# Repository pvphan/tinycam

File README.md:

tinycam
---

This is a simple point-and-shoot camera, mostly an excuse to play with the new [Raspberry Pi High Quality camera](https://www.raspberrypi.org/products/raspberry-pi-high-quality-camera/) and ~~maybe~~ **also** a simple PCB for battery management.
The code is a very simple python script wrapping `raspistill`.
CAD is in [FreeCAD](https://www.freecadweb.org/), and any PCBs designed will be [KiCAD](https://kicad-pcb.org/).

Hardware requirements:

- [Raspberry Pi Zero W ($25)](https://www.amazon.com/CanaKit-Raspberry-Wireless-Official-Supply/dp/B071L2ZQZX/)
- [Samsung Evo+ 32 GB microSD card ($9)](https://www.amazon.com/gp/product/B00WR4IJBE)
- [iUniker 2.8" display ($23)](https://www.amazon.com/gp/product/B07H8ZY89H/)
- [Raspberry Pi High Quality camera ($50)](https://www.pishop.us/product/raspberry-pi-hq-camera/?src=raspberrypi)
- [Telephoto lens for HQ camera ($63)](https://www.pishop.us/product/16mm-telephoto-lens-for-raspberry-pi-hq-camera/)
- [Adafruit PowerBoost 1000 Charger ($20)](https://www.adafruit.com/product/2465)
- [tinycam PCB (~$35 to build)](pcb/)

#### next TODO:

- v2 of chassis to support button trigger and battery management
- auto upload to gphotos a la [eshmu/gphotos-upload](https://github.com/eshmu/gphotos-upload)
- support sleep / wake mode
- gallery mode (for local delete)

#### maybe later TODO:

- support video capture mode
- Qt overlay on top of preview for mode switching or adjusting 'manual' controls

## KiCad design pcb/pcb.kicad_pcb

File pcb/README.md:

PCB
---

**WARNING: as of 2020-10-04, this design does not yet work! There is at least one significant deficiency in the PCB layout around the boost converter (TPS61090). I'm still working through the issues, but here are some links to seemingly related problems:**

- [Adafruit board with similar symptoms](https://forums.adafruit.com/viewtopic.php?f=19&t=110556&start=15)
- [TI forum - TPS61090: short circuits at SW pin 3,4 after working for some time](https://e2e.ti.com/support/power-management/f/196/t/642142?TPS61090-short-circuits-at-SW-pin-3-4-after-working-for-some-time)

PCB designed in KiCAD, BOM in DigiKey importable format ([pcb.csv](pcb.csv)).
The PCB is [shared on OSHPark](https://oshpark.com/shared_projects/fBtFeIY9), cost is $11.90 for 3x board with normal prototyping service.

### 3D Model:

### Schematic:

### PCB Front:

### PCB Back:

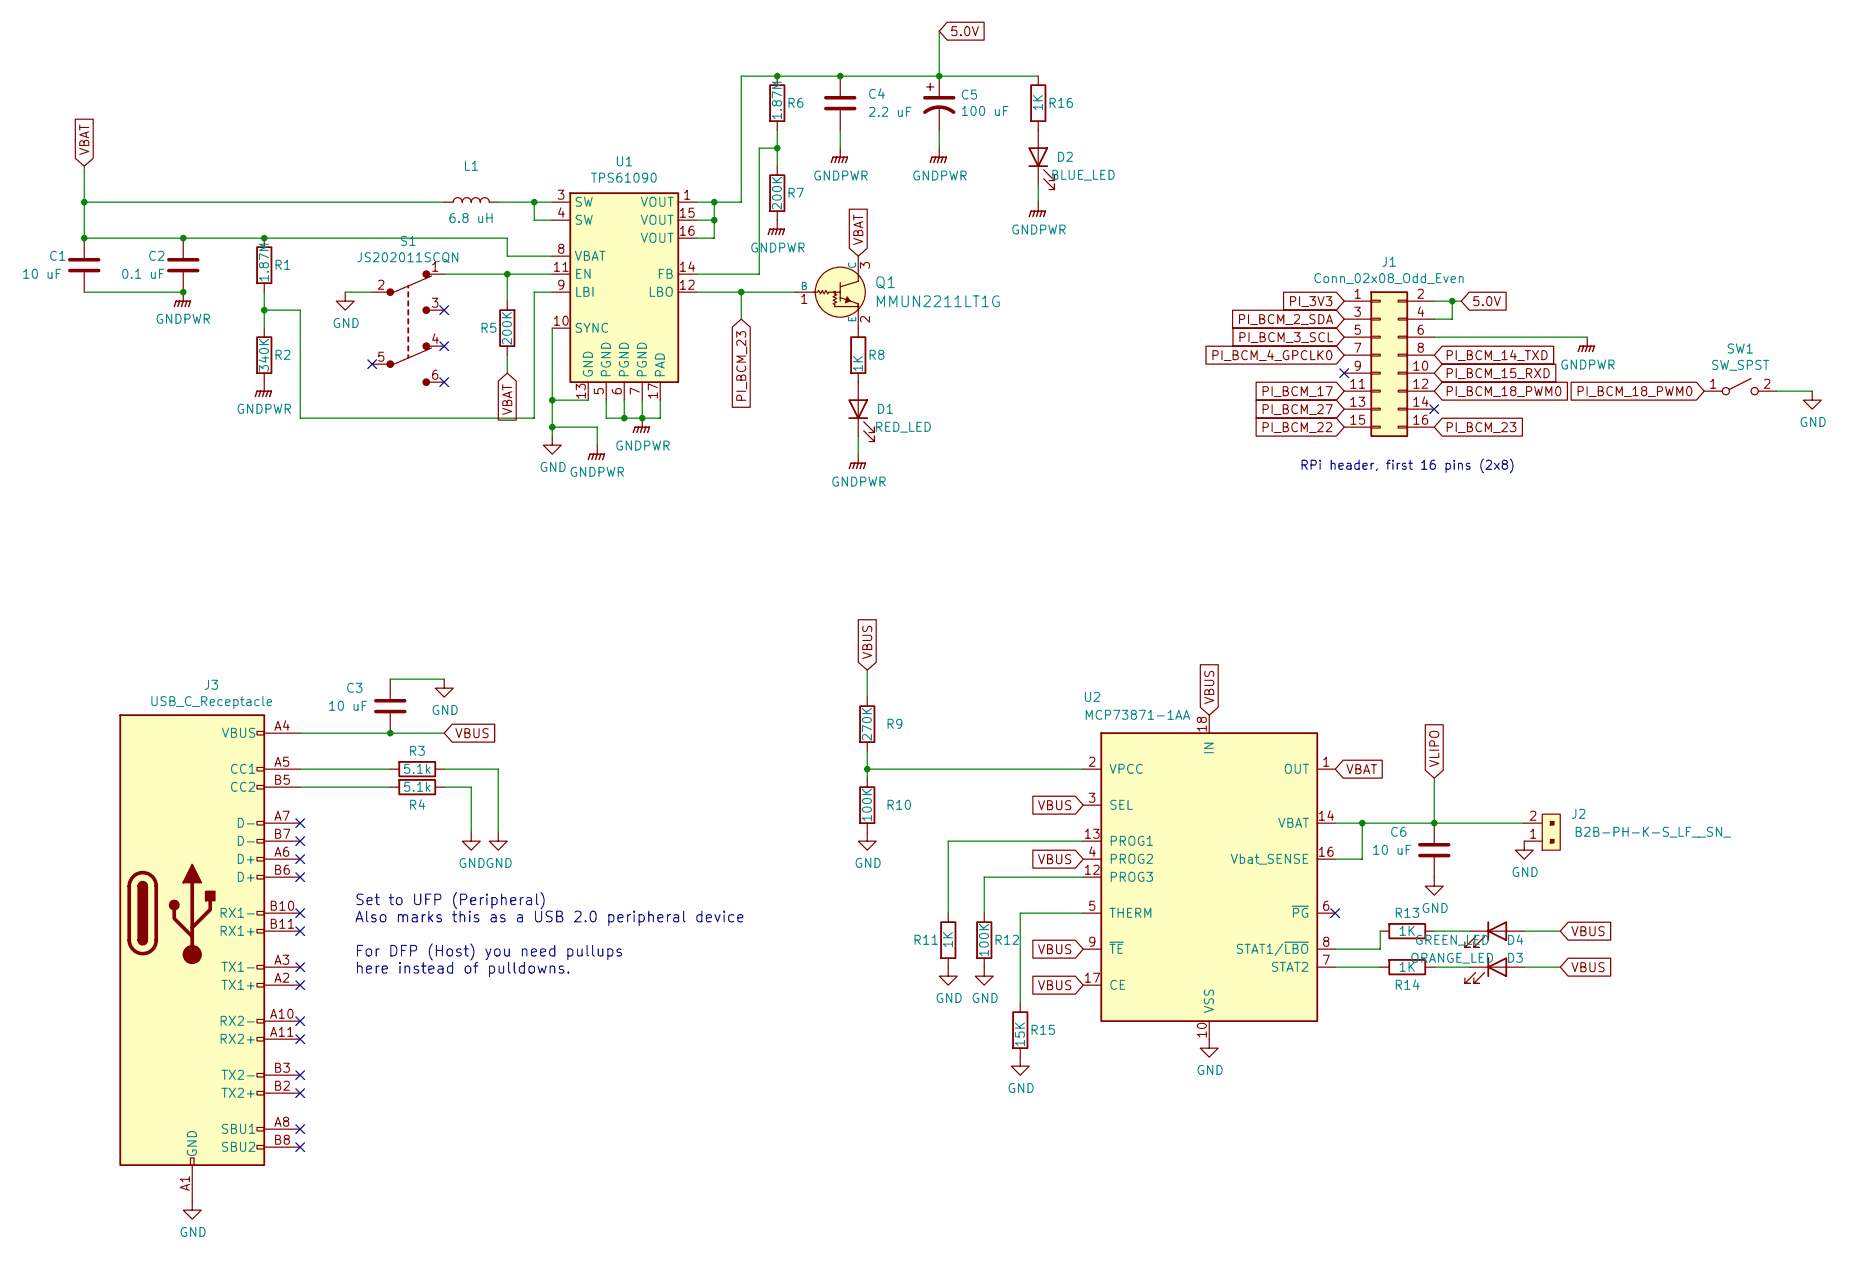
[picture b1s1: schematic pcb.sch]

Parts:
C1, C3, C6: 10 uF; C_0805_2012Metric
C2: 0.1 uF; C_0805_2012Metric
C4: 2.2 uF; C_0805_2012Metric
C5: 100 uF; CP_EIA-6032-20_AVX-F
D1: RED_LED; LED_0805_2012Metric
D2: BLUE_LED; LED_0805_2012Metric
D3: ORANGE_LED; LED_0805_2012Metric
D4: GREEN_LED; LED_0805_2012Metric
J1: Conn_02x08_Odd_Even; PinSocket_2x08_P2.54mm_Vertical
J2: B2B-PH-K-S_LF__SN_; PinHeader_1x2_P2mm_Drill1mm; MPN B2B-PH-K-S(LF)(SN); Digi-Key_PN 455-1704-ND
J3: USB_C_Receptacle; USB-C_Female_E8124-015-01
L1: 6.8 uH; L_Wuerth_WE-PD2-Typ-L
Q1: MMUN2211LT1G; SOT-23-3; MPN MMUN2133LT1G; Digi-Key_PN MMUN2133LT1GOSCT-ND
R1, R6: 1.87M; R_0805_2012Metric
R2: 340K; R_0805_2012Metric
R3, R4: 5.1k; R_0805_2012Metric
R5, R7: 200K; R_0805_2012Metric
R8, R11, R13, R14, R16: 1K; R_0805_2012Metric
R9: 270K; R_0805_2012Metric
R10, R12: 100K; R_0805_2012Metric
R15: 15K; R_0805_2012Metric
S1: JS202011SCQN; SW_DPDT_CK_JS202011JCQN; MPN JS202011SCQN; Digi-Key_PN 401-2002-1-ND
SW1: SW_SPST; FP11SPA1B1TP00
U1: TPS61090; Texas_S-PVQFN-N16_EP2.7x2.7mm_ThermalVias
U2: MCP73871-1AA; QFN-20-1EP_4x4mm_P0.5mm_EP2.5x2.5mm

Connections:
5.0V: C4.1, C5.1, J1.2, J1.4, R6.1, R16.1, U1.1 (VOUT), U1.15 (VOUT), U1.16 (VOUT)
GND: C1.2, C2.2, C3.1, C4.2, C5.2, C6.2, D1.1 (K), D2.1 (K), J1.6, J2.1, J3.A1 (GND), J3.A12 (GND), J3.B1 (GND), J3.B12 (GND), R2.2, R3.1, R4.1, R7.2, R10.2, R11.2, R12.2, R15.2, S1.2, SW1.2 (B), U1.5 (PGND), U1.6 (PGND), U1.7 (PGND), U1.10 (SYNC), U1.13 (GND), U1.17 (PAD), U2.10 (VSS), U2.11 (VSS), U2.21 (VSS)
unnamed: D1.2 (A), R8.2
unnamed: D2.2 (A), R16.2
unnamed: D3.1 (K), R13.1
unnamed: D4.1 (K), R14.1
unnamed: J3.A5 (CC1), R3.2
unnamed: J3.B5 (CC2), R4.2
unnamed: L1.2, U1.3 (SW), U1.4 (SW)
unnamed: Q1.2 (E), R8.1
unnamed: R1.2, R2.1, U1.9 (LBI)
unnamed: R5.2, S1.1, U1.11 (EN)
unnamed: R6.2, R7.1, U1.14 (FB)
unnamed: R9.2, R10.1, U2.2 (VPCC)
unnamed: R11.1, U2.13 (PROG1)
unnamed: R12.1, U2.12 (PROG3)
unnamed: R13.2, U2.8 (STAT1/~LBO~)
unnamed: R14.2, U2.7 (STAT2)
unnamed: R15.1, U2.5 (THERM)
PI_3V3: J1.1
PI_BCM_2_SDA: J1.3
PI_BCM_3_SCL: J1.5
PI_BCM_4_GPCLK0: J1.7
PI_BCM_14_TXD: J1.8
PI_BCM_15_RXD: J1.10
PI_BCM_17: J1.11
PI_BCM_18_PWM0: J1.12, SW1.1 (A)
PI_BCM_22: J1.15
PI_BCM_23: J1.16, Q1.1 (B), U1.12 (LBO)
PI_BCM_27: J1.13
VBAT: C1.1, C2.1, L1.1, Q1.3 (C), R1.1, R5.1, U1.8 (VBAT), U2.1 (OUT), U2.20 (OUT)
VBUS: C3.2, D3.2 (A), D4.2 (A), J3.A4 (VBUS), J3.A9 (VBUS), J3.B4 (VBUS), J3.B9 (VBUS), R9.1, U2.3 (SEL), U2.4 (PROG2), U2.9 (~TE), U2.17 (CE), U2.18 (IN), U2.19 (IN)
VLIPO: C6.1, J2.2, U2.14 (VBAT), U2.15 (VBAT), U2.16 (Vbat_SENSE)

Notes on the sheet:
RPi header, first 16 pins (2x8)
Set to UFP (Peripheral) Also marks this as a USB 2.0 peripheral device For DFP (Host) you need pullups here instead of pulldowns.

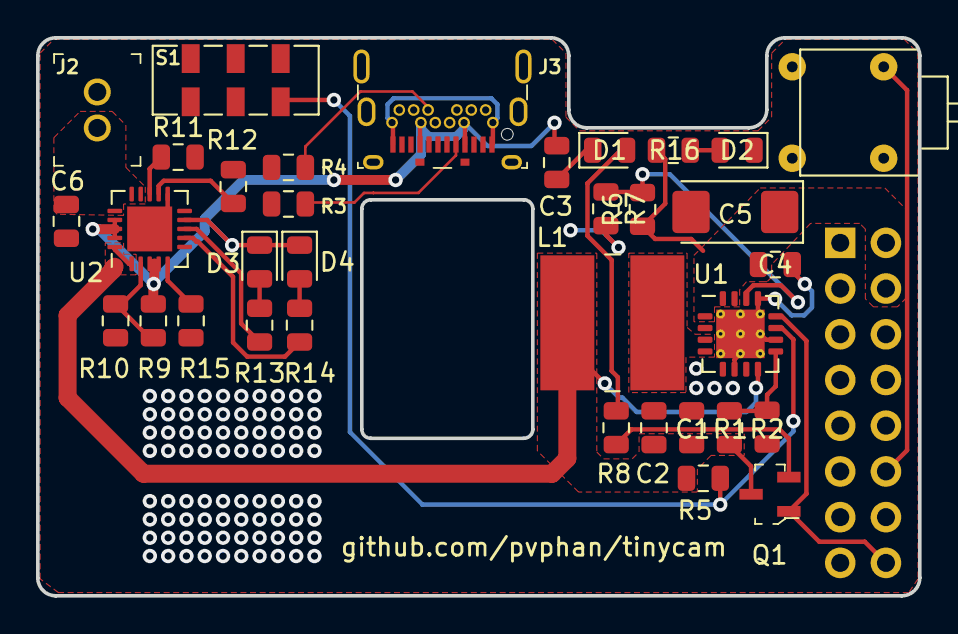
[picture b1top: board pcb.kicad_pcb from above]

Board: 2 copper layers, 49.0 x 31.0 mm, 35 parts (1 on the bottom side), 24 nets.

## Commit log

2020-08-02 added README
2020-08-09 added CAD and image for v1
2020-08-10 started positioning models for v2 chassis
2020-08-16 added initial pcb files
2020-08-17 excluding unused kicad files, added start of schematic with reference
2020-08-17 added some more components
2020-08-20 first pass of schematic complete
2020-08-22 updated schematic a bit, going to delete reference
2020-08-22 netlist has a bug it seems
2020-08-22 removed temp schematic
2020-08-22 pcb is compiling again
2020-08-22 rough positioning of components
2020-08-22 cleaned up layout a little
2020-08-22 in work, PCB layup
2020-08-22 added PCB models
2020-08-23 checkin
2020-08-23 added IMU script
2020-08-23 updated cut profile fillets, 4 corners now the same
2020-08-24 updated cuts and placements, all 0805 SMD
2020-08-24 updated pcb a little
2020-08-24 layed most of the traces
2020-08-24 finished v1 of pcb
2020-08-24 added digikey BOM, finalized v1 layout
2020-08-24 added PCB media files
2020-08-24 fixed README references
2020-08-24 reformated README
2020-08-24 shared board on OSHPark, linked
2020-08-26 updated populated PCB
2020-08-27 fixed some mistakes
2020-08-31 designing case, still in work
2020-09-05 revd to v1.1
2020-09-05 cleaned up a few traces
2020-09-05 increased track widths for power
2020-09-05 updated PCB, oshpark link, and media
2020-09-12 camera case design complete, not yet test printed
2020-09-15 moved output, added stencil (90%)
2020-09-15 moved pcb BOM to outputs
2020-10-05 added warning, still need to fix board
2020-11-22 updated PCB following boost converter design guidelines
2020-11-22 a little cleanup
2020-12-13 updated schematic
